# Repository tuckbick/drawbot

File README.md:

# DrawBot CoreXY Controller & Plotter

## Overview

DrawBot is a custom, ESP32-based controller board and large-format CoreXY pen plotter.

This project was built to scale up the traditional desktop plotter experience. By moving to a custom ESP32 PCB running FluidNC, this iteration eliminates the need for multiple microcontrollers and messy wiring, wrapping WiFi control, SD card hosting, and heavy-duty motor driving into one clean package.

## Project Planning

A "living document" used to keep track of the ongoing planning, component sourcing, and build progress for this project can be found here:

* **[DrawBot Planning Spreadsheet](https://docs.google.com/spreadsheets/d/1DZCe1eKOiRGR80yqyA4uuKFQJ7K6CPcNbJUIT71Rvy4/edit)**

## Inspiration

The first iteration of this build was heavily inspired by the amazing [Plottermap project by Volzo](https://volzo.de/posts/plottermap/).

Volzo's original electronics used a dual-Arduino Nano setup running [GRBL](https://github.com/gnea/grbl/wiki), with a co-processor to handle Stallguard endstops. Since the exact frame specs weren't provided, I reverse-engineered my best guess for the physical construction. For this next-generation build, I am keeping that same physical frame but completely overhauling the electronics to a single-board ESP32 solution.

## The Machine (Hardware)

The physical plotter is designed for large-scale artwork:

* **Frame:** 1m x 1.5m V-Slot extruded aluminum with 3D printed joints.
* **Workspace:** Comfortably accommodates canvases and paper at least 24" x 40".
* **Kinematics:** CoreXY motion system driven by standard belts, pulleys, and idlers.
* **Motors:** 2x NEMA 23 stepper motors for slinging the heavy X/Y gantry, and 1x NEMA 17 for the Z-axis pen lift.
* **External Peripherals:** Support for physical limit switches, a dedicated 24V laser attachment port, and a UART expansion port for future upgrades.

## The Electronics (Controller)

The custom KiCad PCB is designed to be a plug-and-play brain for the machine:

* **Microcontroller:** ESP32 (DevKitC-32).
* **Firmware:** Runs [FluidNC](http://wiki.fluidnc.com/en/home) (a next-gen port of GRBL), which easily handles the CoreXY kinematics and adds native support for TMC SPI configuration.
* **Connectivity:** The ESP32 provides WiFi for remote monitoring and control via a FluidNC web UI.
* **Storage:** An onboard Micro SD card reader hosts the G-code project files locally so your computer doesn't have to stay plugged in for a 10-hour plot.
* **Stepper Drivers:** 3x TMC5160 StepStick modules. These easily provide the juice needed for the NEMA 23 motors.
* **Clean Wiring:** The stepper motor phases are routed out through standard RJ45 jacks, allowing you to use cheap, shielded Cat6 Ethernet cables to wire up the gantry.
* **Power:** Runs on a single 24V power supply (split into motor, laser, and logic domains), stepped down to 5V/3.3V using an MP1584 buck converter.

## Repository Contents

* `/drawbot.kicad_pro` - Main KiCad project file.
* `/*.kicad_sch` - Hierarchical schematic files (Power Delivery, Microcontroller, Stepper Drivers, IO Connectors).
* `/drawbot.kicad_pcb` - The physical PCB layout.
* `/libs/` - Custom footprint and symbol libraries used in the design.
* `/pdf/` - Exported PDF versions of the schematic and PCB layout for quick viewing.

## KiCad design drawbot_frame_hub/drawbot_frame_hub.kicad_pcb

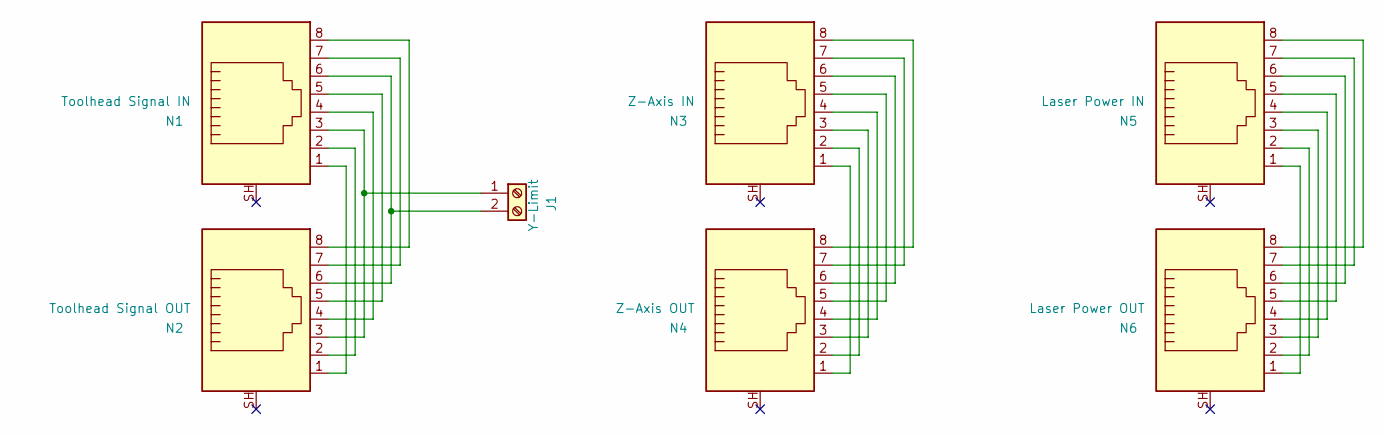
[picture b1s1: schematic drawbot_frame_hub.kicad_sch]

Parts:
J1: Y-Limit; TerminalBlock_Xinya_XY308-2.54-2P_1x02_P2.54mm_Horizontal
N1: Toolhead Signal IN; RJ45_HALO_HFJ11-x2450HRL_Horizontal
N2: Toolhead Signal OUT; RJ45_HALO_HFJ11-x2450HRL_Horizontal
N3: Z-Axis IN; RJ45_HALO_HFJ11-x2450HRL_Horizontal
N4: Z-Axis OUT; RJ45_HALO_HFJ11-x2450HRL_Horizontal
N5: Laser Power IN; RJ45_HALO_HFJ11-x2450HRL_Horizontal
N6: Laser Power OUT; RJ45_HALO_HFJ11-x2450HRL_Horizontal

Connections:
unnamed: J1.1, N1.3, N2.3
unnamed: J1.2, N1.6, N2.6
unnamed: N1.1, N2.1
unnamed: N1.2, N2.2
unnamed: N1.4, N2.4
unnamed: N1.5, N2.5
unnamed: N1.7, N2.7
unnamed: N1.8, N2.8
unnamed: N3.1, N4.1
unnamed: N3.2, N4.2
unnamed: N3.3, N4.3
unnamed: N3.4, N4.4
unnamed: N3.5, N4.5
unnamed: N3.6, N4.6
unnamed: N3.7, N4.7
unnamed: N3.8, N4.8
unnamed: N5.1, N6.1
unnamed: N5.2, N6.2
unnamed: N5.3, N6.3
unnamed: N5.4, N6.4
unnamed: N5.5, N6.5
unnamed: N5.6, N6.6
unnamed: N5.7, N6.7
unnamed: N5.8, N6.8

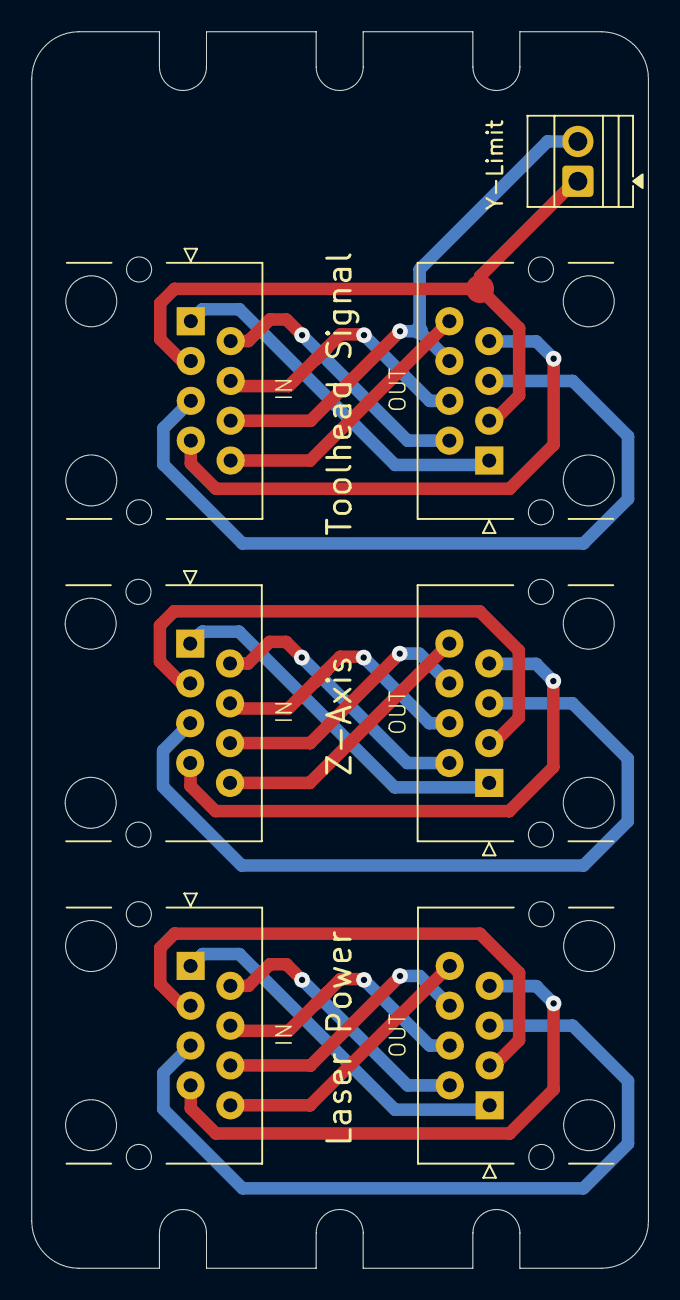
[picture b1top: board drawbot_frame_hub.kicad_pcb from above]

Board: 2 copper layers, 39.3 x 78.9 mm, 7 parts (0 on the bottom side), 24 nets.

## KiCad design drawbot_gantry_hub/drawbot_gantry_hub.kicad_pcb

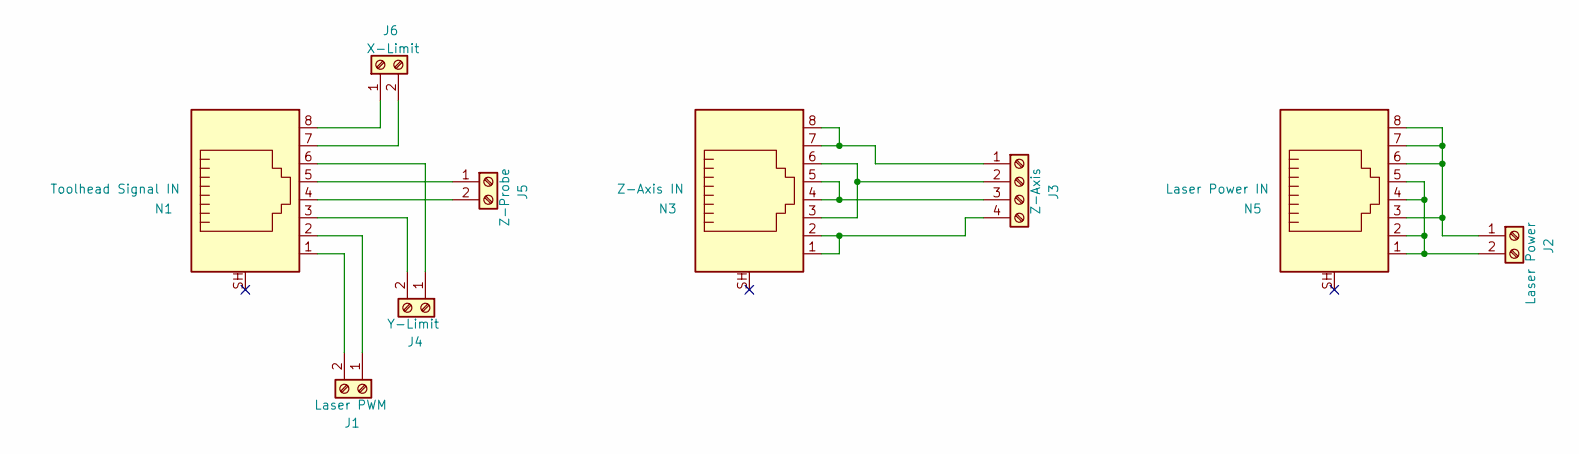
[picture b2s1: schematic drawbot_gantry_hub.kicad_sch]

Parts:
J1: Laser PWM; TerminalBlock_Xinya_XY308-2.54-2P_1x02_P2.54mm_Horizontal
J2: Laser Power; TerminalBlock_RND_205-00045_1x02_P5.00mm_Horizontal
J3: Z-Axis; TerminalBlock_RND_205-00047_1x04_P5.00mm_Horizontal
J4: Y-Limit; TerminalBlock_Xinya_XY308-2.54-2P_1x02_P2.54mm_Horizontal
J5: Z-Probe; TerminalBlock_Xinya_XY308-2.54-2P_1x02_P2.54mm_Horizontal
J6: X-Limit; TerminalBlock_Xinya_XY308-2.54-2P_1x02_P2.54mm_Horizontal
N1: Toolhead Signal IN; RJ45_HALO_HFJ11-x2450HRL_Horizontal
N3: Z-Axis IN; RJ45_HALO_HFJ11-x2450HRL_Horizontal
N5: Laser Power IN; RJ45_HALO_HFJ11-x2450HRL_Horizontal

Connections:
unnamed: J1.1, N1.2
unnamed: J1.2, N1.1
unnamed: J2.1, N5.3, N5.6, N5.7, N5.8
unnamed: J2.2, N5.1, N5.2, N5.4, N5.5
unnamed: J3.1, N3.7, N3.8
unnamed: J3.2, N3.3, N3.6
unnamed: J3.3, N3.4, N3.5
unnamed: J3.4, N3.1, N3.2
unnamed: J4.1, N1.6
unnamed: J4.2, N1.3
unnamed: J5.1, N1.5
unnamed: J5.2, N1.4
unnamed: J6.1, N1.8
unnamed: J6.2, N1.7

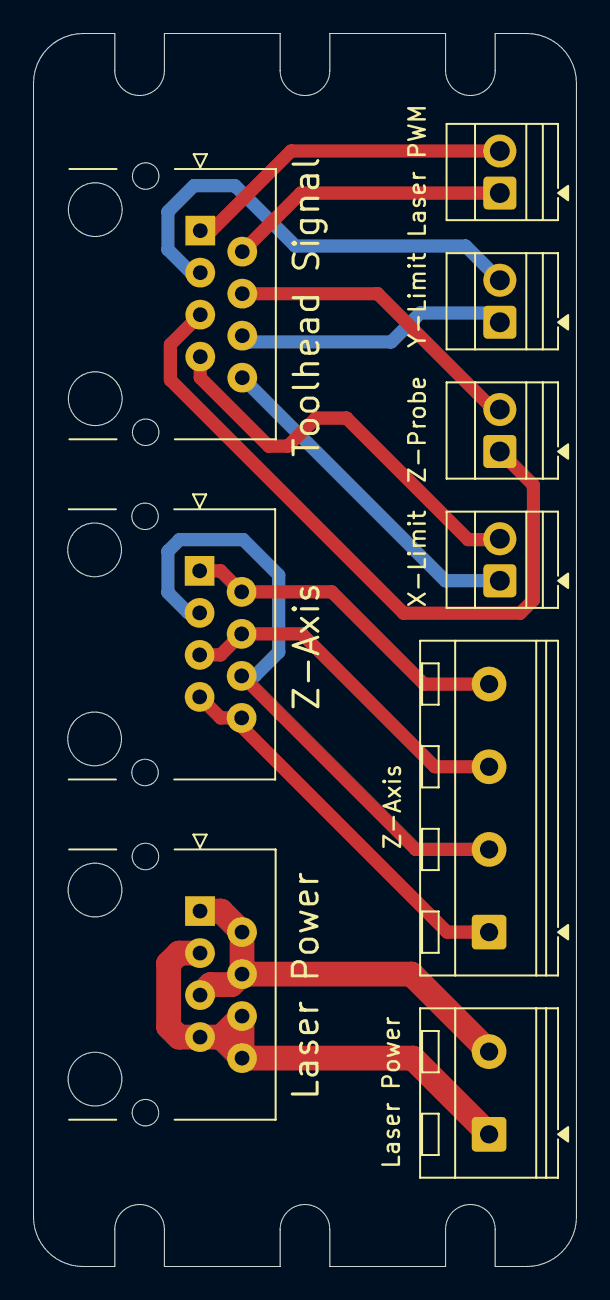
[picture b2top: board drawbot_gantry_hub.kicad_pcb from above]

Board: 2 copper layers, 32.8 x 74.5 mm, 9 parts (0 on the bottom side), 14 nets.

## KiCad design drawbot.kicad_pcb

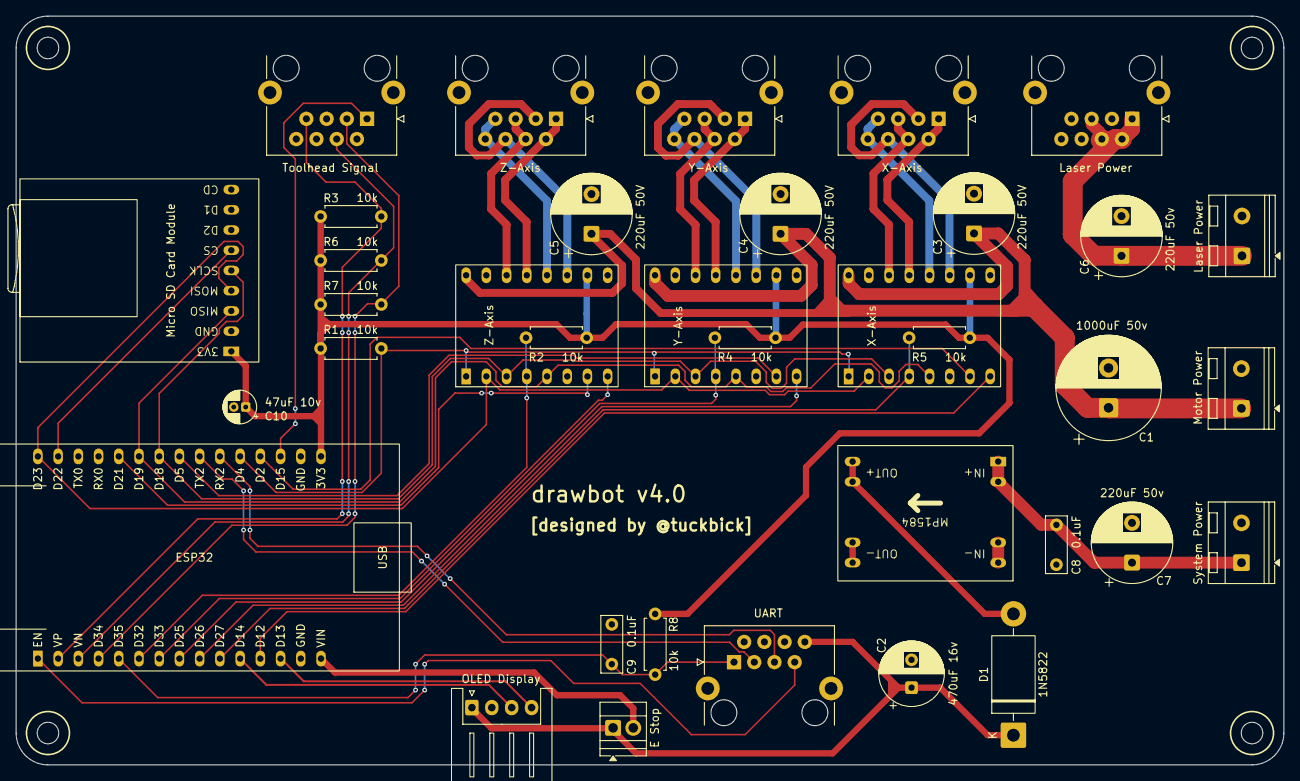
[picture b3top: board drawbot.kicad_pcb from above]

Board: 2 copper layers, 159.2 x 94.0 mm, 36 parts (0 on the bottom side), 44 nets.

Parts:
B1: MP1584
C1: 1000uF 50v; CP_Radial_D13.0mm_P5.00mm
C2: 470uF 16v; CP_Radial_D8.0mm_P3.50mm
C3, C4, C5: 220uF 50V; CP_Radial_D10.0mm_P5.00mm
C6, C7: 220uF 50v; CP_Radial_D10.0mm_P5.00mm
C8, C9: 0.1uF; C_Rect_L7.0mm_W2.5mm_P5.00mm
C10: 47uF 10v; CP_Radial_D4.0mm_P1.50mm
D1: 1N5822; D_DO-201AD_P15.24mm_Horizontal
E1: ESP32; ESP32-DevKitC-32
J1: Motor Power; TerminalBlock_RND_205-00045_1x02_P5.00mm_Horizontal
J2: Laser Power; TerminalBlock_RND_205-00045_1x02_P5.00mm_Horizontal
J3: System Power; TerminalBlock_RND_205-00045_1x02_P5.00mm_Horizontal
J4: OLED Display; JST_XH_S4B-XH-A_1x04_P2.50mm_Horizontal
J5: E Stop; TerminalBlock_Xinya_XY308-2.54-2P_1x02_P2.54mm_Horizontal
N1: X-Axis; RJ45_HALO_HFJ11-x2450HRL_Horizontal
N2: Y-Axis; RJ45_HALO_HFJ11-x2450HRL_Horizontal
N3: Z-Axis; RJ45_HALO_HFJ11-x2450HRL_Horizontal
N4: Laser Power; RJ45_HALO_HFJ11-x2450HRL_Horizontal
N5: Toolhead Signal; RJ45_HALO_HFJ11-x2450HRL_Horizontal
N6: UART; RJ45_HALO_HFJ11-x2450HRL_Horizontal
R1, R2, R3, R4, R5, R6, R7, R8: 10k; R_Axial_DIN0207_L6.3mm_D2.5mm_P7.62mm_Horizontal
SD1: Micro SD Card Module
T1: X-Axis; TMC5160_1
T2: Y-Axis; TMC5160_1
T3: Z-Axis; TMC5160_1

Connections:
+3.3V: C10.1, E1.16 (3V3), R1.2, R2.2, R3.2, R4.2, R5.2, R6.2, R7.2, R8.2, SD1.1 (3.3V), T1.10 (VIO), T2.10 (VIO), T3.10 (VIO)
+5V: C2.1, D1.1 (K), J4.1, J5.1, N6.8
+5V_ESTOP: E1.15 (VIN), J5.2
+LASER_PWR: C6.1, J2.1, N4.1, N4.2, N4.4, N4.5
+MOTOR_PWR: C1.1, C3.1, C4.1, C5.1, J1.1, T1.16 (VM), T2.16 (VM), T3.16 (VM)
ESP_EN: E1.1 (EN), N6.7
GND: B1.3 (VIN-), B1.4 (VIN-), B1.7 (VOUT-), B1.8 (VOUT-), C1.2, C2.2, C3.2, C4.2, C5.2, C6.2, C7.2, C8.1, C9.2, C10.2, E1.14 (GND), E1.17 (GND), J1.2, J2.2, J3.2, J4.2, N1.SH, N2.SH, N3.SH, N4.3, N4.6, N4.7, N4.8, N4.SH, N5.2, N5.5, N5.6, N5.8, N5.SH, N6.2, N6.4, N6.6, N6.SH, SD1.2 (GND), T1.6 (CLK), T1.9 (GND), T1.15 (GND), T2.6 (CLK), T2.9 (GND), T2.15 (GND), T3.6 (CLK), T3.9 (GND), T3.15 (GND)
GPIO_AUX: C9.1, E1.5 (D35), N6.1, R8.1
I2C_SCL: E1.11 (D14), J4.3
I2C_SDA: E1.13 (D13), J4.4
LASER_PWM: E1.18 (D15), N5.1
MOT_EN: E1.20 (D4), R1.1, T1.1 (EN), T2.1 (EN), T3.1 (EN)
unnamed: B1.5 (VOUT+), B1.6 (VOUT+), D1.2 (A)
unnamed: B1.1 (VIN+), B1.2 (VIN+), C7.1, C8.2, J3.1
SD_CS: E1.29 (D22), SD1.6 (CS)
SPI_MISO: E1.25 (D19), SD1.3 (MISO), T1.5 (MISO), T2.5 (MISO), T3.5 (MISO)
SPI_MOSI: E1.30 (D23), SD1.4 (MOSI), T1.2 (MOSI), T2.2 (MOSI), T3.2 (MOSI)
SPI_SCK: E1.24 (D18), SD1.5 (SCLK), T1.3 (SCK), T2.3 (SCK), T3.3 (SCK)
UART_RX: E1.21 (RX2), N6.5
UART_TX: E1.22 (TX2), N6.3
X_A+: N1.1, N1.2, T1.13 (A1)
X_A-: N1.4, N1.5, T1.14 (A2)
X_B+: N1.3, N1.6, T1.11 (B1)
X_B-: N1.7, N1.8, T1.12 (B2)
X_CS: E1.10 (D27), R5.1, T1.4 (CS)
X_DIR: E1.12 (D12), T1.8 (DIR)
X_LIMIT: E1.2 (VP), N5.7, R3.1
X_STEP: E1.19 (D2), T1.7 (STEP)
Y_A+: N2.1, N2.2, T2.13 (A1)
Y_A-: N2.4, N2.5, T2.14 (A2)
Y_B+: N2.3, N2.6, T2.11 (B1)
Y_B-: N2.7, N2.8, T2.12 (B2)
Y_CS: E1.8 (D25), R4.1, T2.4 (CS)
Y_DIR: E1.9 (D26), T2.8 (DIR)
Y_LIMIT: E1.4 (D34), N5.3, R7.1
Y_STEP: E1.23 (D5), T2.7 (STEP)
Z_A+: N3.1, N3.2, T3.13 (A1)
Z_A-: N3.4, N3.5, T3.14 (A2)
Z_B+: N3.3, N3.6, T3.11 (B1)
Z_B-: N3.7, N3.8, T3.12 (B2)
Z_CS: E1.6 (D32), R2.1, T3.4 (CS)
Z_DIR: E1.7 (D33), T3.8 (DIR)
Z_PROBE: E1.3 (VN), N5.4, R6.1
Z_STEP: E1.26 (D21), T3.7 (STEP)

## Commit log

2026-03-11 adding belated progress
2026-03-11 adding README
2026-03-18 rearrange and connect everything
    rearrange and connect everything
2026-04-01 DRC resolutions; Final silkscreen adjustments;
2026-04-01 Moving controller project into separate directory
2026-04-02 rename controller project files
2026-04-02 add rj45 to stepper connection boards
2026-04-02 clean up stepper board
2026-04-02 add frame and gantry boards
2026-04-02 add stepper board production files
2026-04-02 add frame board production files
2026-04-02 add gantry board production files
2026-04-02 removing custom symbols and footprints
